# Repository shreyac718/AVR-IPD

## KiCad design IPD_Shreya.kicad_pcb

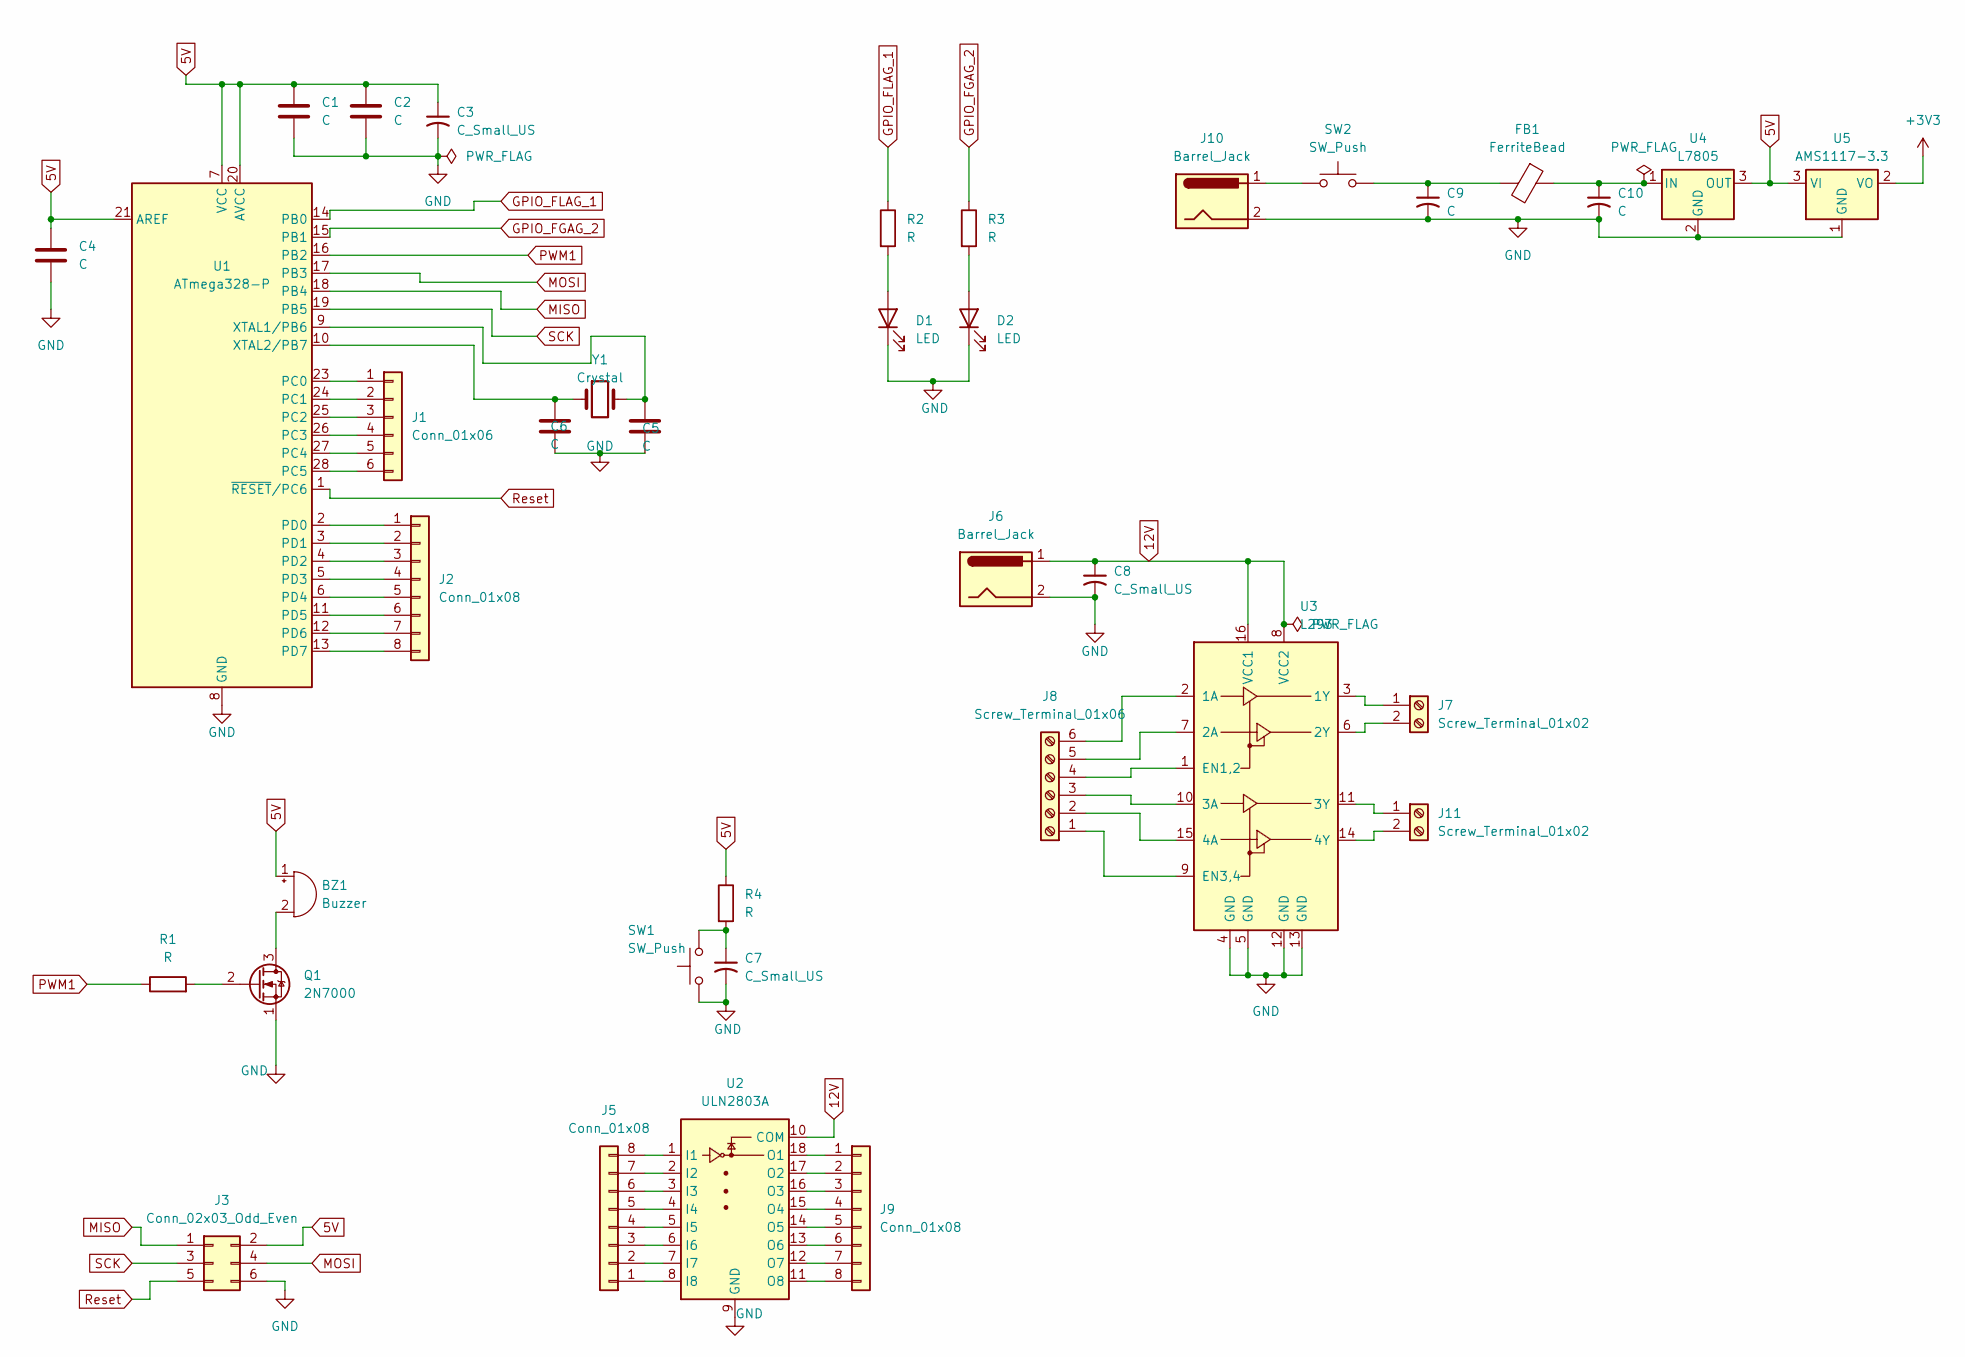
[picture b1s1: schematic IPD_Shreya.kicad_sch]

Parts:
BZ1: Buzzer; Buzzer_12x9.5RM7.6
C1, C2, C4, C5, C6, C9, C10: C; CP_Radial_D7.5mm_P2.50mm
C3, C7, C8: C_Small_US; CP_Radial_D4.0mm_P1.50mm
D1, D2: LED; LED_D8.0mm
FB1: FerriteBead; LairdTech_28C0236-0JW-10
J1: Conn_01x06; PhoenixContact_GMSTBV_2,5_6-GF-7,62_1x06_P7.62mm_Vertical_T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
J2, J5, J9: Conn_01x08; PhoenixContact_GMSTBV_2,5_8-GF-7,62_1x08_P7.62mm_Vertical_T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
J3: Conn_02x03_Odd_Even; IDC-Header_2x03_P2.54mm_Vertical
J6, J10: Barrel_Jack; BarrelJack_CUI_PJ-063AH_Horizontal
J7, J11: Screw_Terminal_01x02; PhoenixContact_GMSTBV_2,5_2-GF-7,62_1x02_P7.62mm_Vertical_T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
J8: Screw_Terminal_01x06; PhoenixContact_GMSTBV_2,5_6-GF-7,62_1x06_P7.62mm_Vertical_T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
Q1: 2N7000; TO-92_Inline
R1, R2, R3, R4: R; R_Axial_DIN0207_L6.3mm_D2.5mm_P7.62mm_Horizontal
SW1, SW2: SW_Push; Panasonic_EVQPUM_EVQPUD
U1: ATmega328-P; DIP-28_W7.62mm
U2: ULN2803A; DIP-18_W7.62mm
U3: L293; DIP-16_W7.62mm
U4: L7805; TO-220-3_Vertical
U5: AMS1117-3.3; SOT-223-3_TabPin2
Y1: Crystal; Crystal_C26-LF_D2.1mm_L6.5mm_Vertical

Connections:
5V: BZ1.1 (+), C1.1, C2.1, C3.1, C4.1, J3.2, R4.1, U1.7 (VCC), U1.20 (AVCC), U1.21 (AREF), U4.3 (OUT), U5.3 (VI)
12V: C8.1, J6.1, U2.10 (COM), U3.8 (VCC2), U3.16 (VCC1)
+3V3: U5.2 (VO)
GND: C1.2, C2.2, C3.2, C4.2, C5.2, C6.2, C7.2, C8.2, C9.2, C10.2, D1.1 (K), D2.1 (K), J3.6, J6.2, J10.2, Q1.1 (S), SW1.1, U1.8 (GND), U1.22 (GND), U2.9 (GND), U3.4 (GND), U3.5 (GND), U3.12 (GND), U3.13 (GND), U4.2 (GND), U5.1 (GND)
GPIO_FGAG_2: R3.1, U1.15 (PB1)
GPIO_FLAG_1: R2.1, U1.14 (PB0)
MISO: J3.1, U1.18 (PB4)
MOSI: J3.4, U1.17 (PB3)
unnamed: BZ1.2 (-), Q1.3 (D)
unnamed: C7.1, R4.2, SW1.2
unnamed: C9.1, FB1.2, SW2.2
unnamed: D1.2 (A), R2.2
unnamed: D2.2 (A), R3.2
unnamed: J1.1, U1.23 (PC0)
unnamed: J1.2, U1.24 (PC1)
unnamed: J1.3, U1.25 (PC2)
unnamed: J1.4, U1.26 (PC3)
unnamed: J1.5, U1.27 (PC4)
unnamed: J1.6, U1.28 (PC5)
unnamed: J2.1, U1.2 (PD0)
unnamed: J2.2, U1.3 (PD1)
unnamed: J2.3, U1.4 (PD2)
unnamed: J2.4, U1.5 (PD3)
unnamed: J2.5, U1.6 (PD4)
unnamed: J2.6, U1.11 (PD5)
unnamed: J2.7, U1.12 (PD6)
unnamed: J2.8, U1.13 (PD7)
unnamed: J5.1, U2.8 (I8)
unnamed: J5.2, U2.7 (I7)
unnamed: J5.3, U2.6 (I6)
unnamed: J5.4, U2.5 (I5)
unnamed: J5.5, U2.4 (I4)
unnamed: J5.6, U2.3 (I3)
unnamed: J5.7, U2.2 (I2)
unnamed: J5.8, U2.1 (I1)
unnamed: J7.1, U3.3 (1Y)
unnamed: J7.2, U3.6 (2Y)
unnamed: J8.1, U3.9 (EN3,4)
unnamed: J8.2, U3.15 (4A)
unnamed: J8.3, U3.10 (3A)
unnamed: J8.4, U3.1 (EN1,2)
unnamed: J8.5, U3.7 (2A)
unnamed: J8.6, U3.2 (1A)
unnamed: J9.1, U2.18 (O1)
unnamed: J9.2, U2.17 (O2)
unnamed: J9.3, U2.16 (O3)
unnamed: J9.4, U2.15 (O4)
unnamed: J9.5, U2.14 (O5)
unnamed: J9.6, U2.13 (O6)
unnamed: J9.7, U2.12 (O7)
unnamed: J9.8, U2.11 (O8)
unnamed: J10.1, SW2.1
unnamed: J11.1, U3.11 (3Y)
unnamed: J11.2, U3.14 (4Y)
unnamed: Q1.2 (G), R1.2
unnamed: C5.1, U1.9 (XTAL1/PB6), Y1.2
unnamed: C6.1, U1.10 (XTAL2/PB7), Y1.1
unnamed: C10.1, FB1.1, U4.1 (IN)
PWM1: R1.1, U1.16 (PB2)
Reset: J3.5, U1.1 (~RESET/PC6)
SCK: J3.3, U1.19 (PB5)

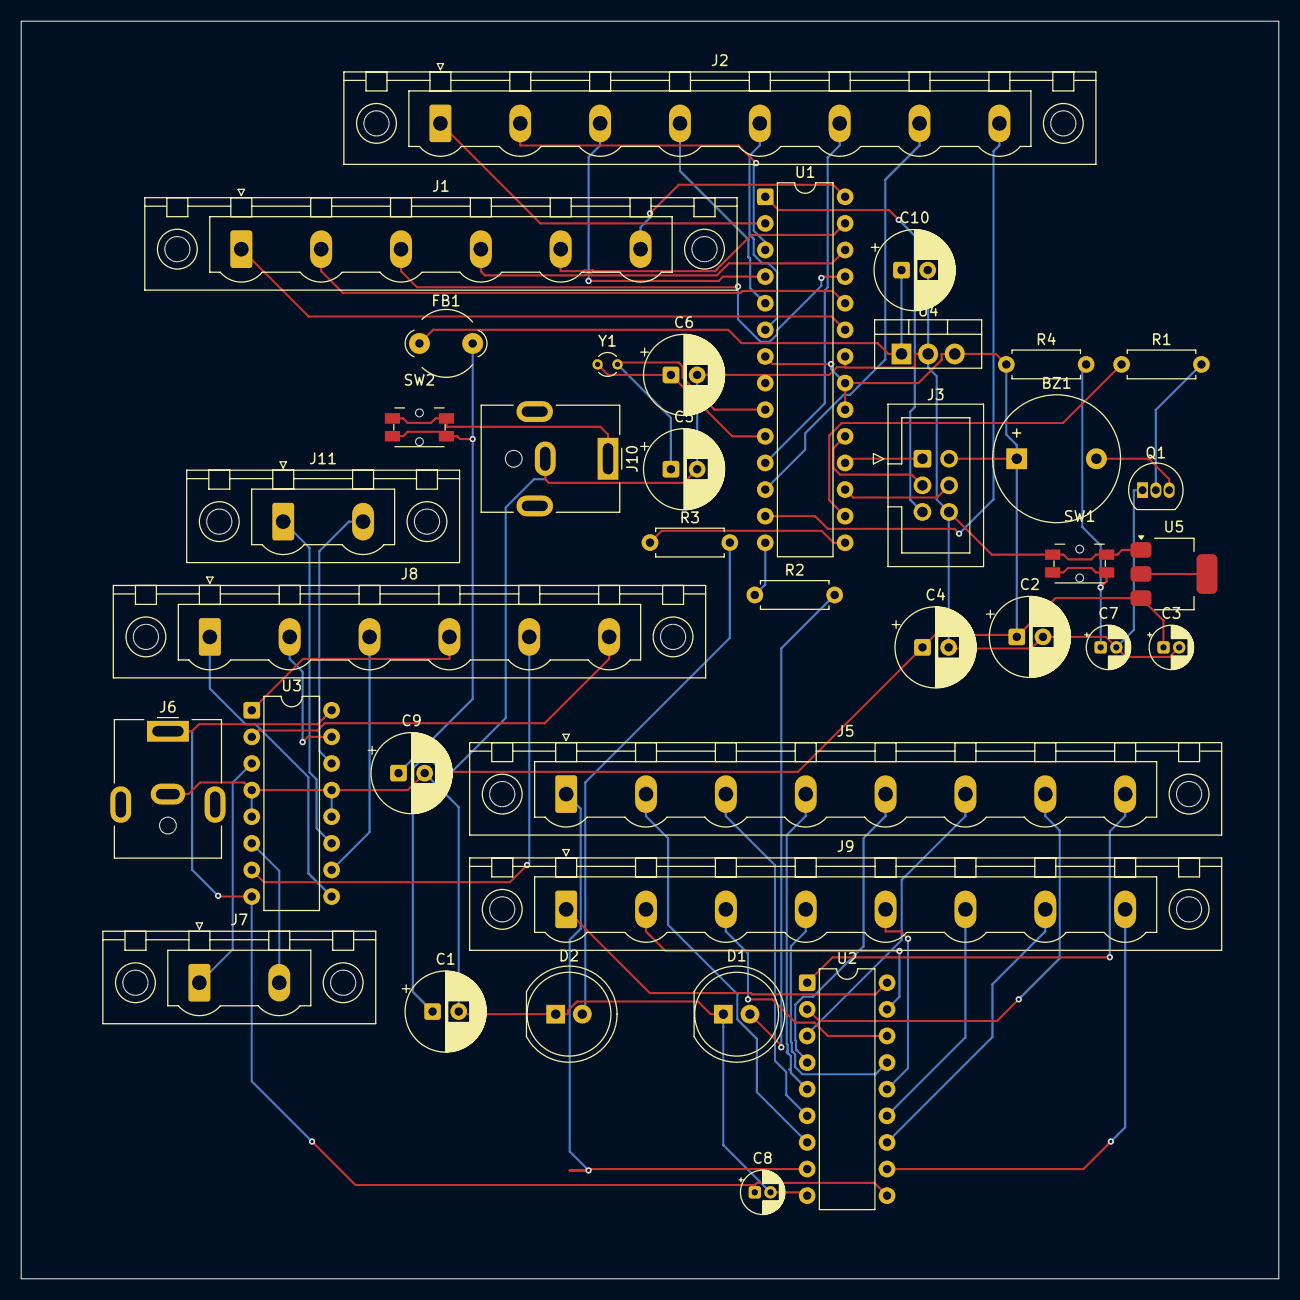
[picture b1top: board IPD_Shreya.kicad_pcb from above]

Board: 2 copper layers, 120.0 x 120.0 mm, 37 parts (0 on the bottom side), 60 nets.
